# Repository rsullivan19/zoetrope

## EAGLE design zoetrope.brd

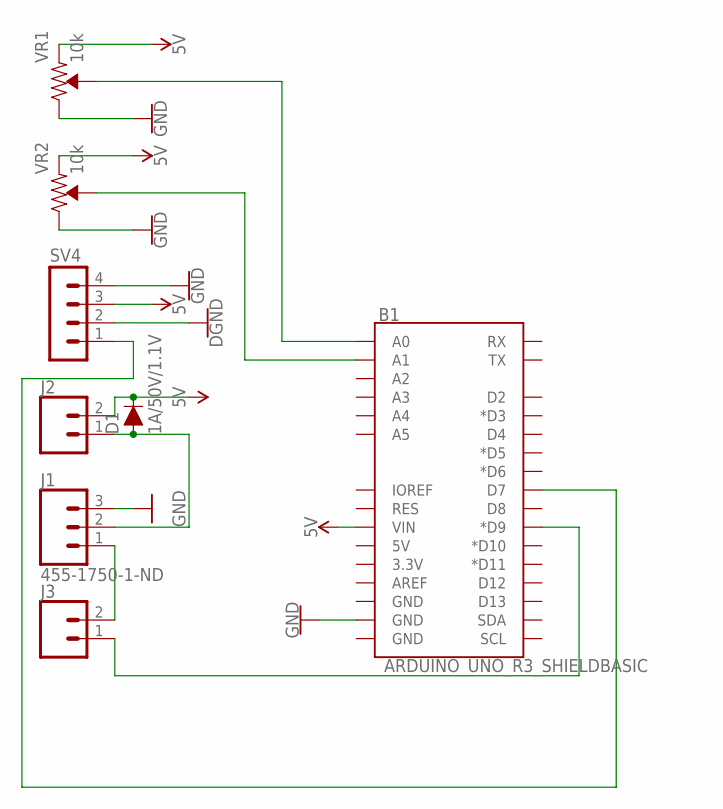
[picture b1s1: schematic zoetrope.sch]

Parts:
B1: ARDUINO_UNO_R3_SHIELDBASIC; UNO_R3_SHIELD
D1: 1A/50V/1.1V; DIODE-1N4001
J1: 455-1750-1-ND; 1X03
J2, J3: CONN_02; 1X02
SV4: MA04-1
VR1, VR2: 10k; TRIMPOT-PTH-3386U

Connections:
5V: B1.VIN, D1.C, J2.2, SV4.3, VR1.1 (CCW), VR2.1 (CCW)
GND: B1.GND@1 (GND), J1.3, SV4.2, SV4.4, VR1.3 (CW), VR2.3 (CW)
unnamed: B1.D7, SV4.1
unnamed: B1.A1, VR2.2 (WIPER)
unnamed: D1.A, J1.2, J2.1
unnamed: J1.1, J3.2
unnamed: B1.D9 (*D9), J3.1
unnamed: B1.A0, VR1.2 (WIPER)

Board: 2 copper layers, 8 parts (1 on the bottom side), 8 nets, no tracks yet.

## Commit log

2018-09-11 Create motor code
2018-09-11 Update motor code

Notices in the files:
parts and their libraries:
SparkFun-Boards: Licensing: Creative Commons ShareAlike 4.0 International - https://creativecommons.org/licenses/by-sa/4.0
